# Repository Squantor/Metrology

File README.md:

# General Metrology related projects/tools
This repository contains metrology related hardware/software/mechcanical parts. Stuff like tools, jigs, adapters etc.
## Structure
* [electronics](electronics/README.md) contains all the electronic hardware used in the project.
* [software](software/README.md) contains all the software used in the project. This can be embedded, PC/smartphone or test scripts, anything a computer can execute resides here.
* [mechanical](mechanical/README.md) contains all the CAD drawings, mostly 3d printable objects.
* [documentation](documentation/index.md) contains all project documentation, logs, research, papers, datasheets and more.
## Cloning
This repository makes extensive use of submodules, use ```git clone --recurse-submodules https://github.com/Squantor/Metrology.git``` to clone everything in one go.

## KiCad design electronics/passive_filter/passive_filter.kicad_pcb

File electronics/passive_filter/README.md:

# Passive filter and pad
Small filter and pad PCB
## TODO's
Still some things need to be done:
* schematic entry 
* PCB layout
* Review with one night in between
* Produce at [OSHPARK](https://oshpark.com/)
* Assemble
* Test & characterise
* update Readme.md with pictures and BOM

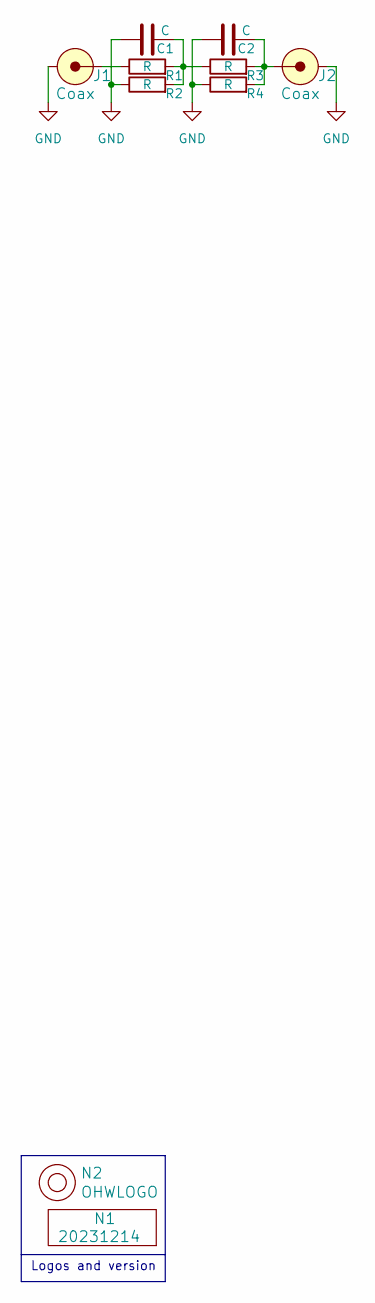
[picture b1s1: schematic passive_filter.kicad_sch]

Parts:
C1, C2: C; C_0402+0603+0805+TH
J1, J2: Coax; coax_edge_1.5_center_5_side
N1: 20231214; Label_Generic
N2: OHWLOGO; OSHW-Symbol_6.7x6mm_SilkScreen
R1, R2, R3, R4: R; R_0805+0603

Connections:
GND: C1.1, C2.1, J1.2, J2.2, R2.1, R4.1
unnamed: C1.2, R1.2, R2.2, R3.1
unnamed: C2.2, J2.1, R3.2, R4.2
unnamed: J1.1, R1.1

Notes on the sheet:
Logos and version

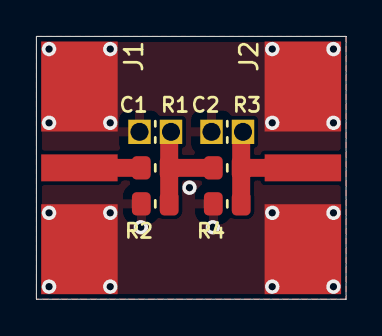
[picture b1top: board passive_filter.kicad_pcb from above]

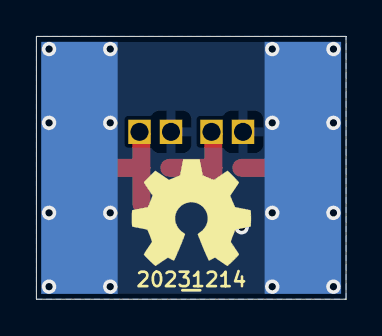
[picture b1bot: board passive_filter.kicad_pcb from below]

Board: 2 copper layers, 17.2 x 14.6 mm, 10 parts (2 on the bottom side), 4 nets.

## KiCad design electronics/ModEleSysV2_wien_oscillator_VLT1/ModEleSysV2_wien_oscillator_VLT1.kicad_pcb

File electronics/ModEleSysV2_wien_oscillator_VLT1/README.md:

# Wien bridge oscillator
Wien bridge oscillator based on the linear technology application note 43 figure 47.

## TODO's
Still some things need to be done:
* Fill in this project description
* schematic entry 
* PCB layout
* Review with one night in between
* Produce at [OSHPARK](https://oshpark.com/)
* Assemble
* Test & characterise
* update Readme.md with pictures and BOM

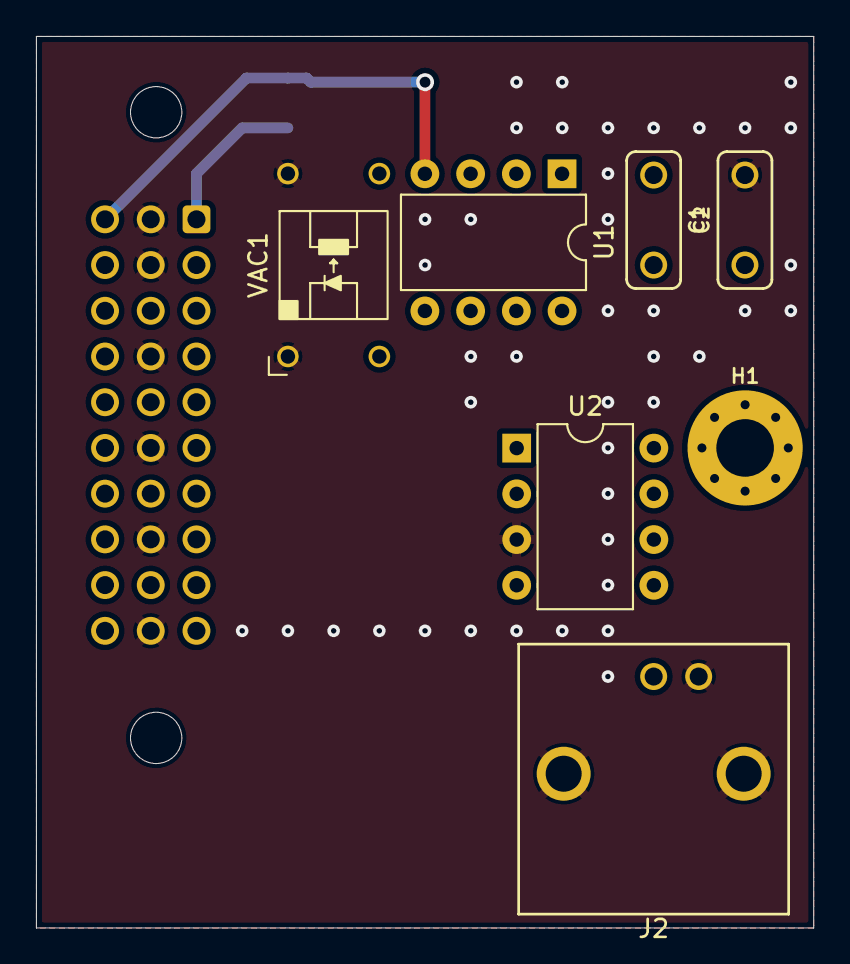
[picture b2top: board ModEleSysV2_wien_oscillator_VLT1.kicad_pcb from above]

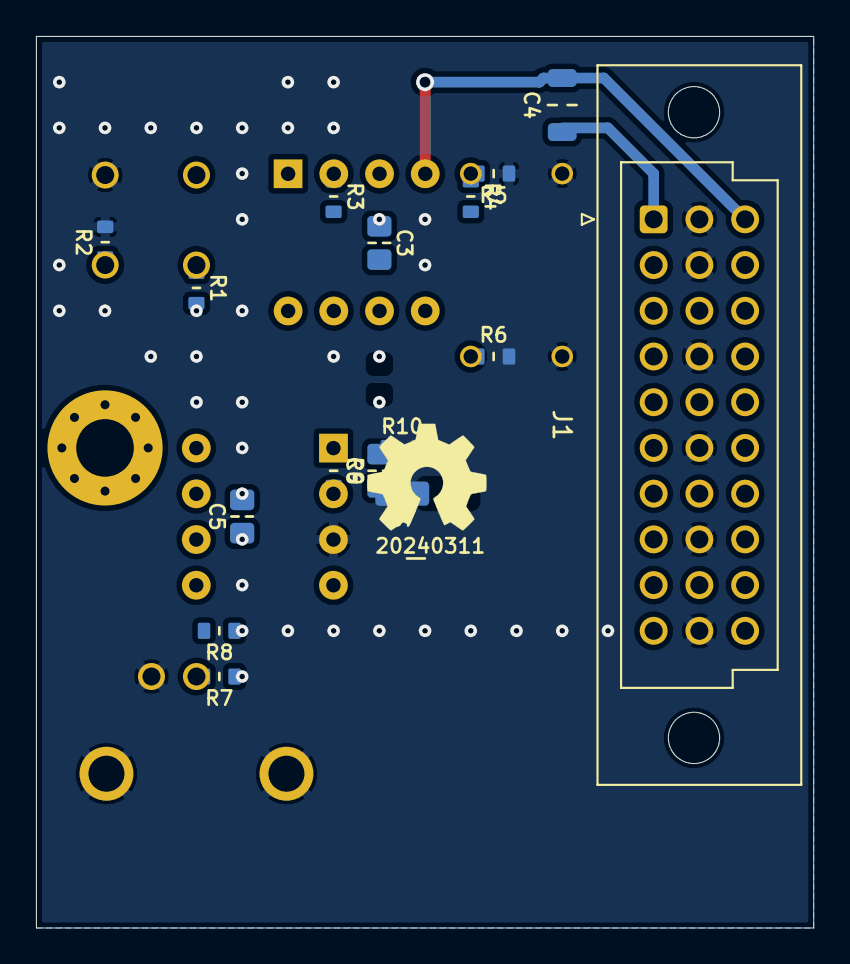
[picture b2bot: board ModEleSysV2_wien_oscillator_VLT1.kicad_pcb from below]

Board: 2 copper layers, 43.2 x 49.5 mm, 25 parts (18 on the bottom side), 13 nets.

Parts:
C1, C2: 47n; C-050-030X100-film
C3, C5, C6: 1uF; C_0805+0603
C4: 10uF; C_1206
C7: 10uF; C_0805+0603
H1: MountingHole; MountingHole_3.2mm_M3_Pad_Via
J1: DIN41612_R3_3x10_Male_Vertical_THT
J2: Coax_shielded; Conn_BNC_RightAngle_TH
N1: 20240311; Label_Generic
N2: OHWLOGO; OSHW-Symbol_6.7x6mm_SilkScreen
R1, R2: 3K; R_0603_hand
R3: 6K8; R_0603_hand
R4: 3K3; R_0603_hand
R5: 220; R_0603_hand
R6: 100; R_0603_hand
R7, R8: 1K2; R_0603_hand
R9: 120K; R_0603_hand
R10: 1K; R_0603_hand
U1: TL081; DIP-8_W7.62mm
U2: LM358; DIP-8_W7.62mm
VAC1: Vactrol; NSL32SR3

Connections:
/+aV: C3.2, C4.1, C5.2, J1.A1 (V+), U1.7 (V+), U2.8 (V+)
/-aV: C3.1, C4.2, C5.1, J1.C1 (V-), U1.4 (V-), U2.4 (V-)
/GAIN_SET: C6.2, R6.2, R9.1, R10.1, U2.1 (OUT1)
/OUT: R1.2, R3.2, R7.1, R8.1, U1.6 (OUT), U2.6 (-IN2), U2.7 (OUT2)
GND: C2.2, J1.B1 (GND), J1.B2 (GND), J1.B4 (GND), J1.B6 (GND), J1.B8 (GND), J1.B10 (GND), J2.2, J2.S, R2.2, R5.1, U2.3 (+IN1), VAC1.1 (C), VAC1.4 (R)
unnamed: C1.2, R1.1
unnamed: C7.1, R10.2
unnamed: J2.1, R7.2, R8.2
unnamed: R4.1, R5.2, VAC1.3 (R)
unnamed: C1.1, C2.1, R2.1, U1.3 (+IN)
unnamed: R3.1, R4.2, U1.2 (-IN)
unnamed: C6.1, C7.2, R9.2, U2.2 (-IN1)
unnamed: R6.1, VAC1.2 (A)

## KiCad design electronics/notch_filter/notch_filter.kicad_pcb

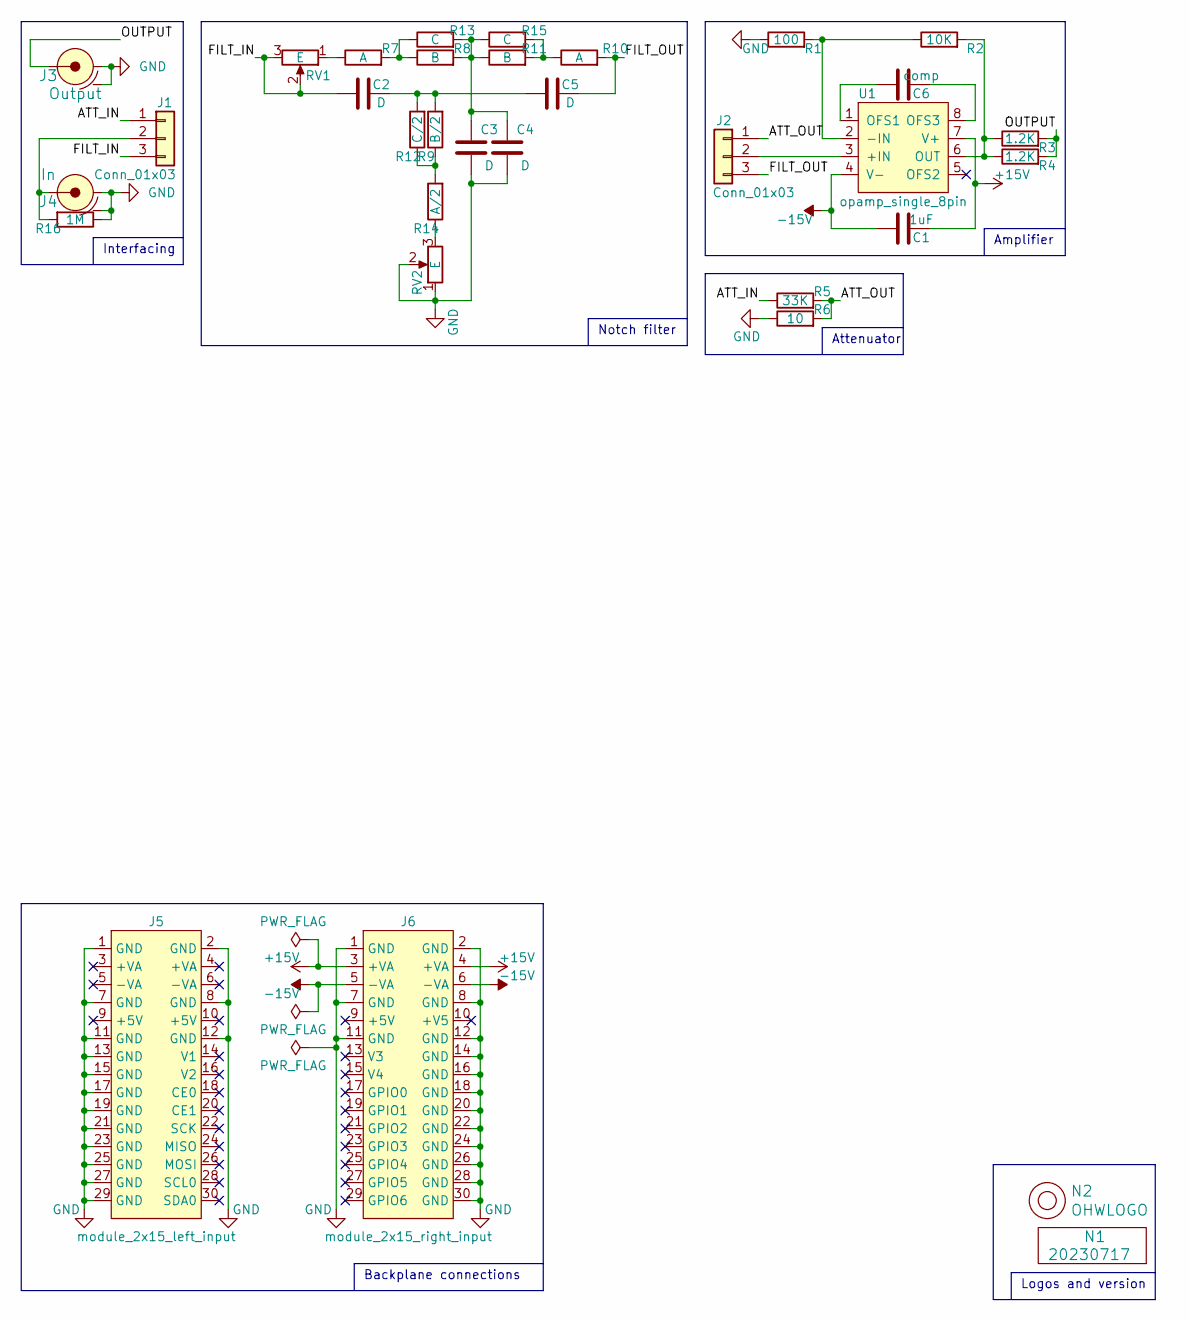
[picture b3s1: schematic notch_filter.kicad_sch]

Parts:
C1: 1uF; C_0805+0603
C2, C3, C4, C5: D; C-050-050X100-0805-3516-film
C6: comp; C_0805+0603
J1, J2: Conn_01x03; JST_PH_B3B-PH-K_1x03_P2.00mm_Vertical
J3: Output; Conn_BNC_RightAngle_TH
J4: In; Conn_BNC_RightAngle_TH
J5: module_2x15_left_input; PinHeader_2x15_P2.54mm_Vertical
J6: module_2x15_right_input; PinHeader_2x15_P2.54mm_Vertical
N1: 20230717; Label_Generic
N2: OHWLOGO; OSHW-Symbol_6.7x6mm_SilkScreen
R1: 100; R_0805+0603
R2: 10K; R_0805+0603
R3, R4: 1.2K; R_0805+0603
R5: 33K; R_0805+0603
R6: 10; R_0805+0603
R7, R10: A; R_0805+0603
R8, R11: B; R_0805+0603
R9: B/2; R_0805+0603
R12: C/2; R_0805+0603
R13, R15: C; R_0805+0603
R14: A/2; R_0805+0603
R16: 1M; R_0805+0603
RV1, RV2: E; Potentiometer_Bourns_3296W_Vertical
U1: opamp_single_8pin; DIP-8_W7.62mm_Socket

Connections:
+15V: C1.2, J6.3 (+VA), J6.4 (+VA), U1.7 (V+)
-15V: C1.1, J6.5 (-VA), J6.6 (-VA), U1.4 (V-)
/ATT_IN: J1.1, R5.1
/ATT_OUT: J2.1, R5.2, R6.2
/FILT_IN: C2.1, J1.3, RV1.2, RV1.3
/FILT_OUT: C5.2, J2.3, R10.2
/OUTPUT: J3.1, R3.2, R4.2
GND: C3.1, C4.1, J3.2, J3.S, J4.2, J4.S, J5.1 (GND), J5.2 (GND), J5.7 (GND), J5.8 (GND), J5.11 (GND), J5.12 (GND), J5.13 (GND), J5.15 (GND), J5.17 (GND), J5.19 (GND), J5.21 (GND), J5.23 (GND), J5.25 (GND), J5.27 (GND), J5.29 (GND), J6.1 (GND), J6.2 (GND), J6.7 (GND), J6.8 (GND), J6.11 (GND), J6.12 (GND), J6.14 (GND), J6.16 (GND), J6.18 (GND), J6.20 (GND), J6.22 (GND), J6.24 (GND), J6.26 (GND), J6.28 (GND), J6.30 (GND), R1.1, R6.1, R16.1, RV2.1, RV2.2
unnamed: C2.2, C5.1, R9.2, R12.2
unnamed: C3.2, C4.2, R8.2, R11.1, R13.2, R15.1
unnamed: J1.2, J4.1, R16.2
unnamed: J2.2, U1.3 (+IN)
unnamed: R7.1, RV1.1
unnamed: R10.1, R11.2, R15.2
unnamed: R9.1, R12.1, R14.2
unnamed: R7.2, R8.1, R13.1
unnamed: R14.1, RV2.3
unnamed: R1.2, R2.1, U1.2 (-IN)
unnamed: C6.1, U1.1 (OFS1)
unnamed: C6.2, U1.8 (OFS3)
unnamed: R2.2, R3.1, R4.1, U1.6 (OUT)

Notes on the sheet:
Logos and version
Amplifier
Backplane connections
Attenuator
Interfacing
Notch filter

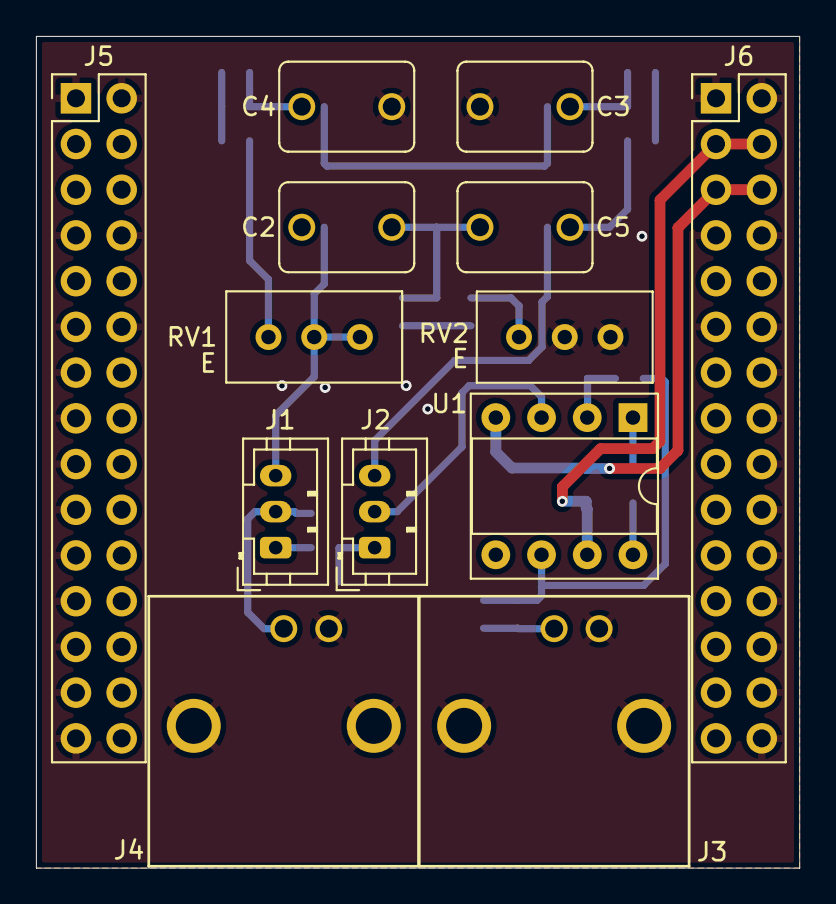
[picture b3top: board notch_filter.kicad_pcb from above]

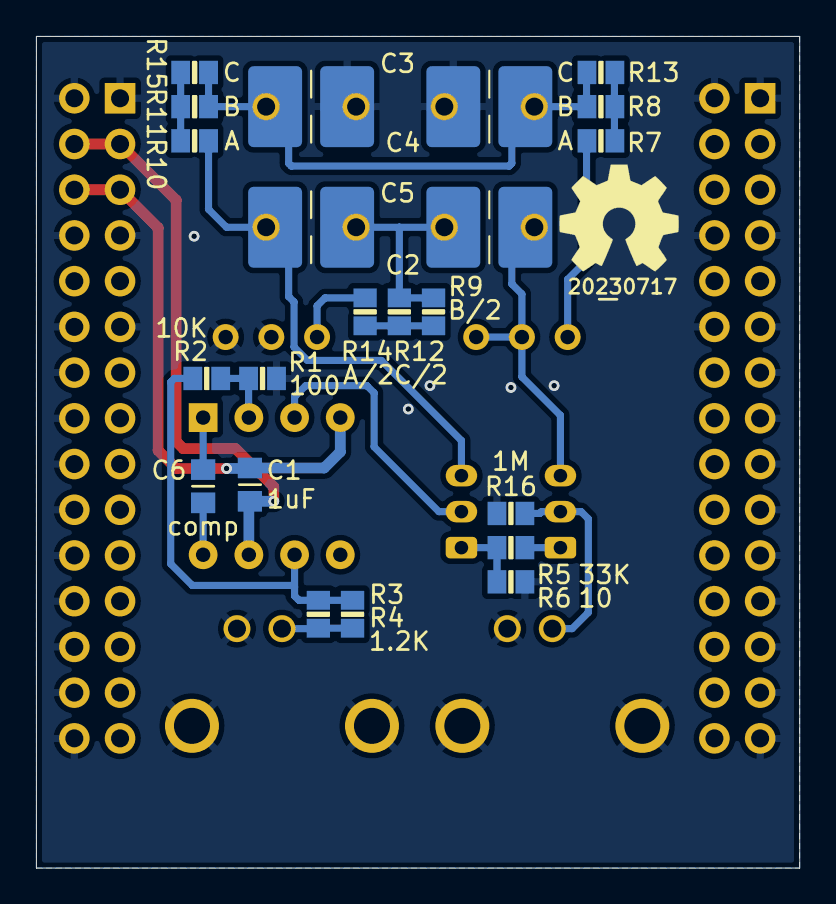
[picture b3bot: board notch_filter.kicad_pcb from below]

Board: 2 copper layers, 42.4 x 46.2 mm, 33 parts (20 on the bottom side), 21 nets.

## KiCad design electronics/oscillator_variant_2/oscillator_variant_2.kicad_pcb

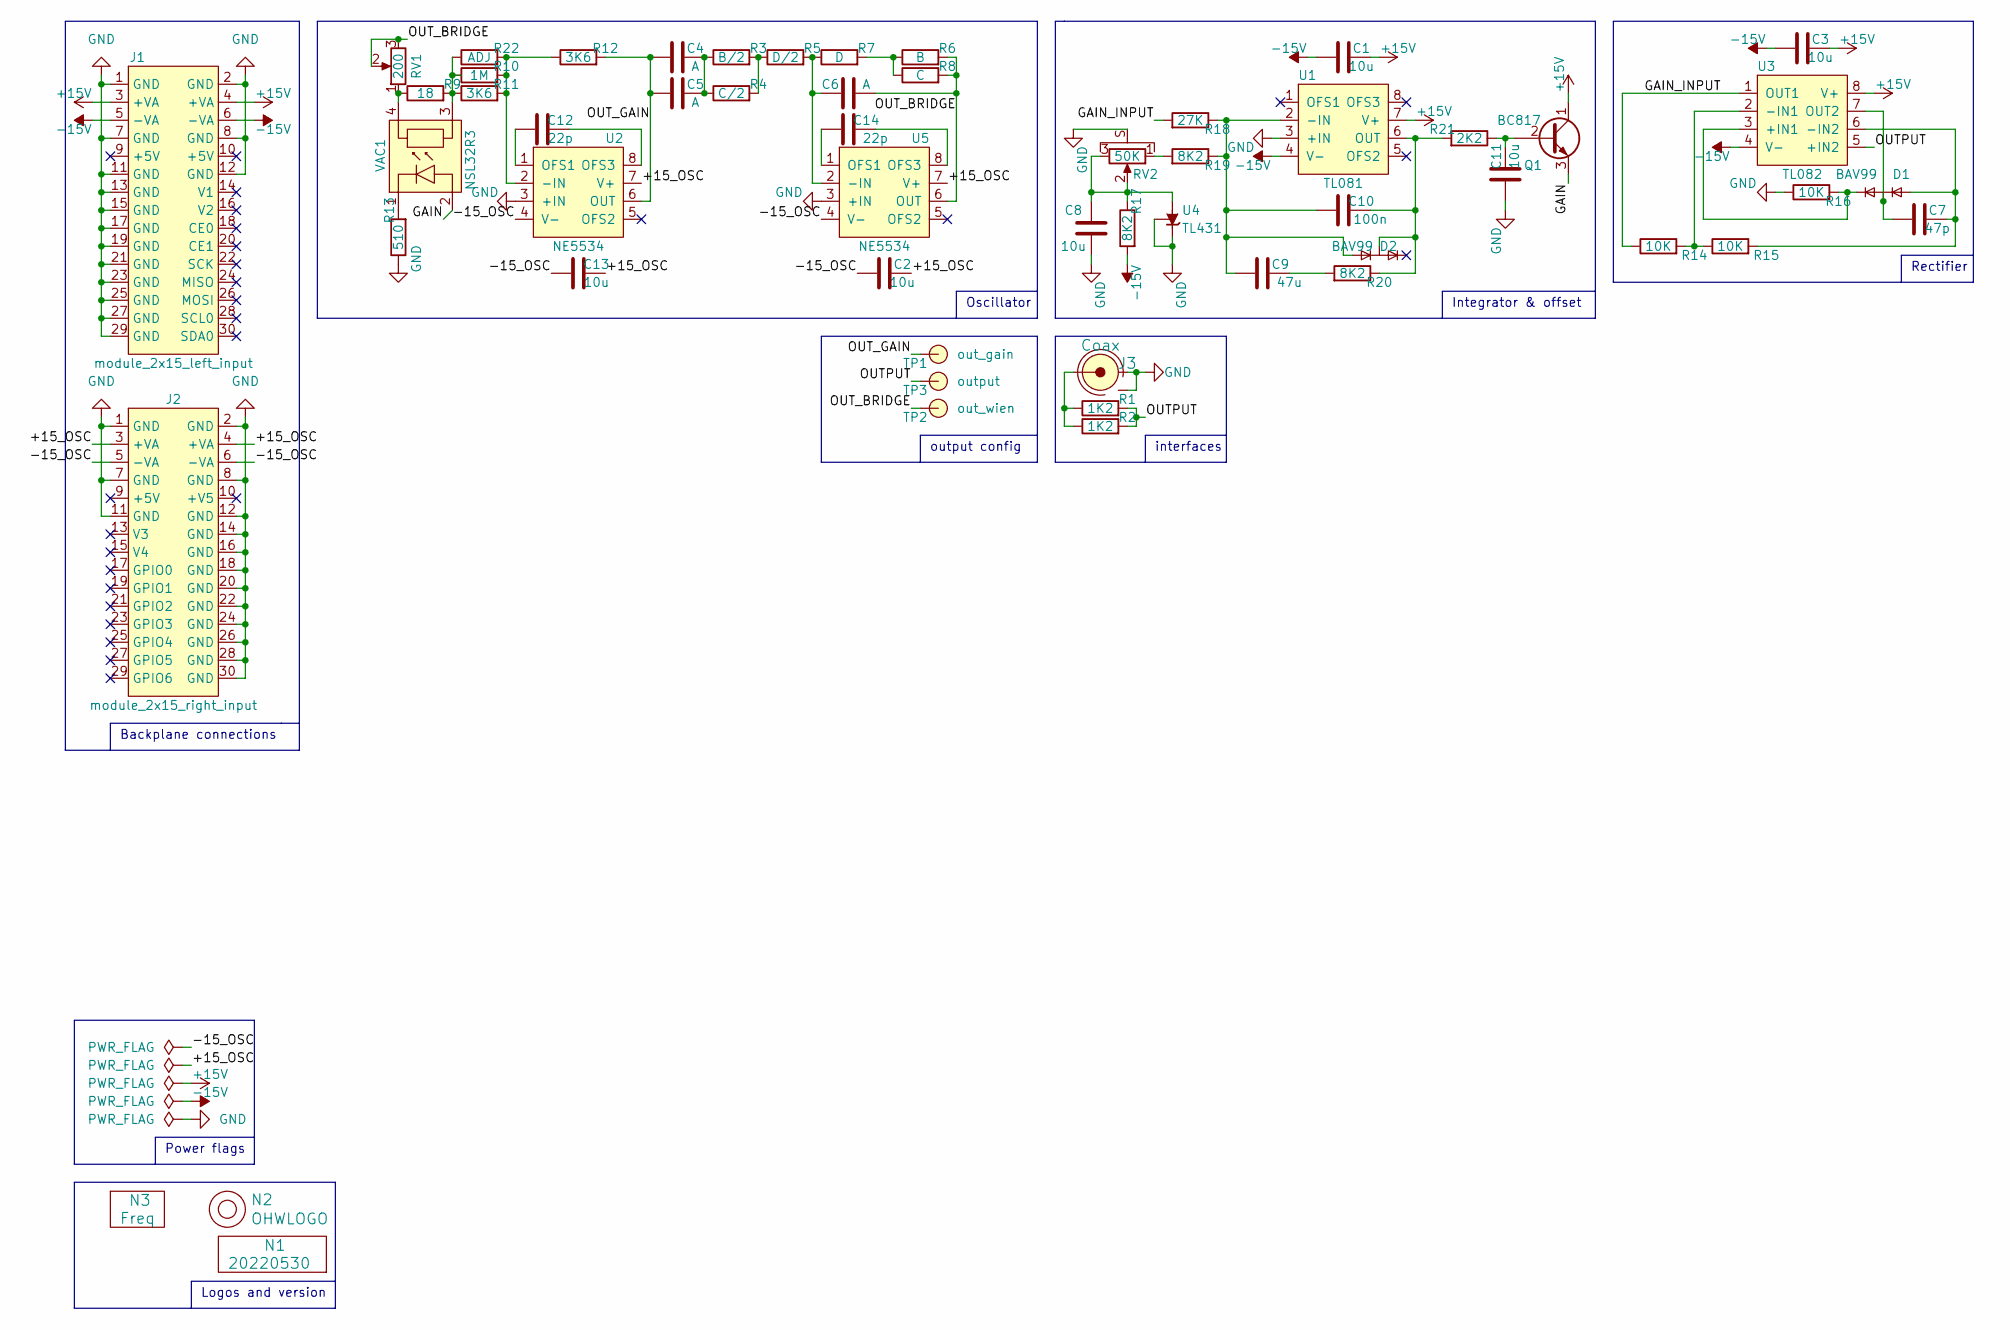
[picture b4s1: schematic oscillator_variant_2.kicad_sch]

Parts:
C1, C2, C3, C8, C11, C13: 10u; C_0805+0603
C4, C5, C6: A; C-050-050X100-0805-3516-film
C7: 47p; C_0805+0603
C9: 47u; C-050-030X100-film
C10: 100n; C-050-030X100-film
C12, C14: 22p; C_0805+0603
D1, D2: BAV99; SOT23-3
J1: module_2x15_left_input; module_2x15_left
J2: module_2x15_right_input; module_2x15_right
J3: Coax; Conn_BNC_RightAngle_TH
N1: 20220530; Label_Generic
N2: OHWLOGO; OSHW-Symbol_6.7x6mm_SilkScreen
N3: Freq; Label_Note_medium
Q1: BC817; SOT23-3
R1, R2: 1K2; R_0603_hand
R3: B/2; R_0805+0603
R4: C/2; R_0805+0603
R5: D/2; R_0805+0603
R6: B; R_0805+0603
R7: D; R_0805+0603
R8: C; R_0805+0603
R9: 18; R_0805+0603
R10: 1M; R_0805+0603
R11, R12: 3K6; R_0805+0603
R13: 510; R_0603_hand
R14, R15, R16: 10K; R_0603_hand
R17, R19, R20: 8K2; R_0603_hand
R18: 27K; R_0603_hand
R21: 2K2; R_0603_hand
R22: ADJ; R_0805+0603
RV1: 200; Potentiometer_Bourns_3296W_Vertical
RV2: 50K; POT_ALPS_RK09K111
TP1: out_gain; TestPoint_hole_H04R07
TP2: out_wien; TestPoint_hole_H04R07
TP3: output; TestPoint_hole_H04R07
U1: TL081; DIP-8_W7.62mm_Socket
U2, U5: NE5534; DIP-8_W7.62mm_Socket
U3: TL082; DIP-8_W7.62mm_Socket
U4: TL431; SOT23-3
VAC1: NSL32R3; NSL32SR3

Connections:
+15V: C1.2, C3.2, J1.3 (+VA), J1.4 (+VA), Q1.1 (C), U1.7 (V+), U3.8 (V+)
-15V: C1.1, C3.1, J1.5 (-VA), J1.6 (-VA), R17.2, U1.4 (V-), U3.4 (V-)
/+15_OSC: C2.2, C13.2, J2.3 (+VA), J2.4 (+VA), U2.7 (V+), U5.7 (V+)
/-15_OSC: C2.1, C13.1, J2.5 (-VA), J2.6 (-VA), U2.4 (V-), U5.4 (V-)
/GAIN: Q1.3 (E), VAC1.2 (A)
/GAIN_INPUT: R14.1, R18.2, U3.1 (OUT1)
/OUTPUT: R1.2, R2.2, TP3.1, U3.5 (+IN2)
/OUT_BRIDGE: C6.2, R6.2, R8.2, RV1.2, RV1.3, TP2.1, U5.6 (OUT)
/OUT_GAIN: C4.1, C5.1, R12.2, TP1.1, U2.6 (OUT)
GND: C8.1, C11.1, J1.1 (GND), J1.2 (GND), J1.7 (GND), J1.8 (GND), J1.11 (GND), J1.12 (GND), J1.13 (GND), J1.15 (GND), J1.17 (GND), J1.19 (GND), J1.21 (GND), J1.23 (GND), J1.25 (GND), J1.27 (GND), J1.29 (GND), J2.1 (GND), J2.2 (GND), J2.7 (GND), J2.8 (GND), J2.11 (GND), J2.12 (GND), J2.14 (GND), J2.16 (GND), J2.18 (GND), J2.20 (GND), J2.22 (GND), J2.24 (GND), J2.26 (GND), J2.28 (GND), J2.30 (GND), J3.2, J3.S, R13.1, R16.1, RV2.S (shield), U1.3 (+IN), U2.3 (+IN), U4.1 (REF), U4.3 (K), U5.3 (+IN)
unnamed: C4.2, C5.2, R3.1, R4.1
unnamed: C6.1, R5.2, R7.1, U5.2 (-IN)
unnamed: C7.1, D1.3 (K1A2), U3.7 (OUT2)
unnamed: C7.2, D1.1 (A1), R15.2, U3.6 (-IN2)
unnamed: C8.2, R17.1, RV2.2, RV2.3, U4.2 (A)
unnamed: C9.2, R20.2
unnamed: C9.1, C10.1, D2.1 (A1), R18.1, R19.1, U1.2 (-IN)
unnamed: C10.2, D2.3 (K1A2), R20.1, R21.2, U1.6 (OUT)
unnamed: C11.2, Q1.2 (B), R21.1
unnamed: C12.1, U2.1 (OFS1)
unnamed: C12.2, U2.8 (OFS3)
unnamed: C14.1, U5.1 (OFS1)
unnamed: C14.2, U5.8 (OFS3)
unnamed: D1.2 (K2), R16.2, U3.3 (+IN1)
unnamed: J3.1, R1.1, R2.1
unnamed: R3.2, R4.2, R5.1
unnamed: R6.1, R7.2, R8.1
unnamed: R9.1, RV1.1, VAC1.4 (R)
unnamed: R9.2, R10.1, R11.1, R22.1, VAC1.3 (R)
unnamed: R10.2, R11.2, R12.1, R22.2, U2.2 (-IN)
unnamed: R13.2, VAC1.1 (C)
unnamed: R14.2, R15.1, U3.2 (-IN1)
unnamed: R19.2, RV2.1

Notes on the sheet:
Backplane connections
Oscillator
Logos and version
interfaces
output config
Power flags
Integrator & offset
Rectifier

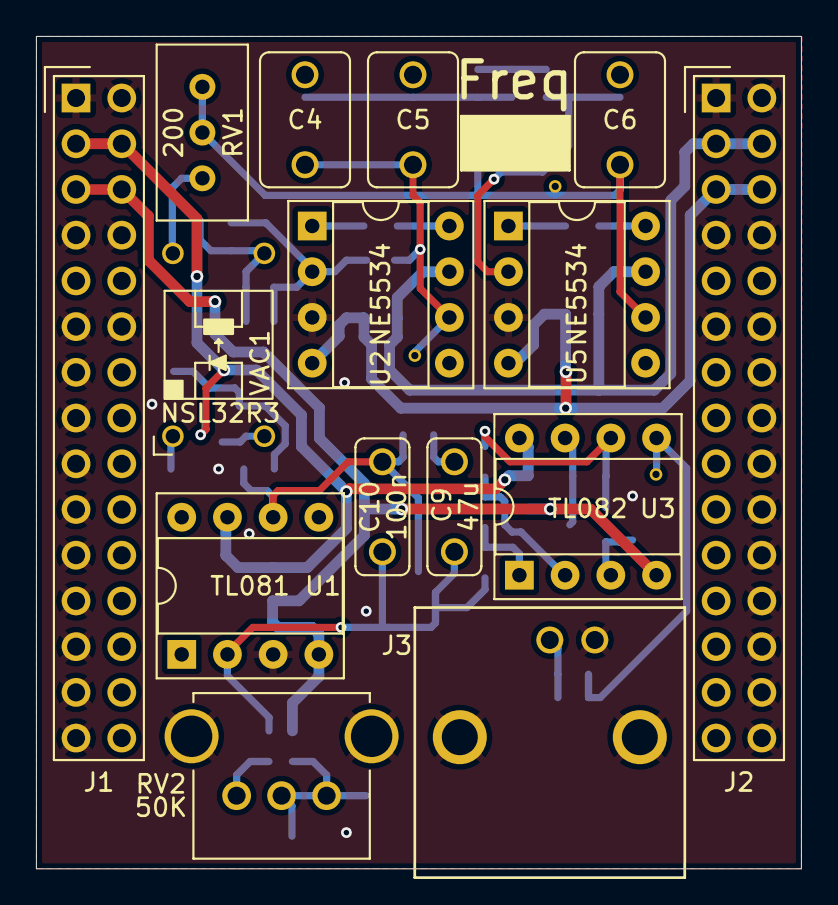
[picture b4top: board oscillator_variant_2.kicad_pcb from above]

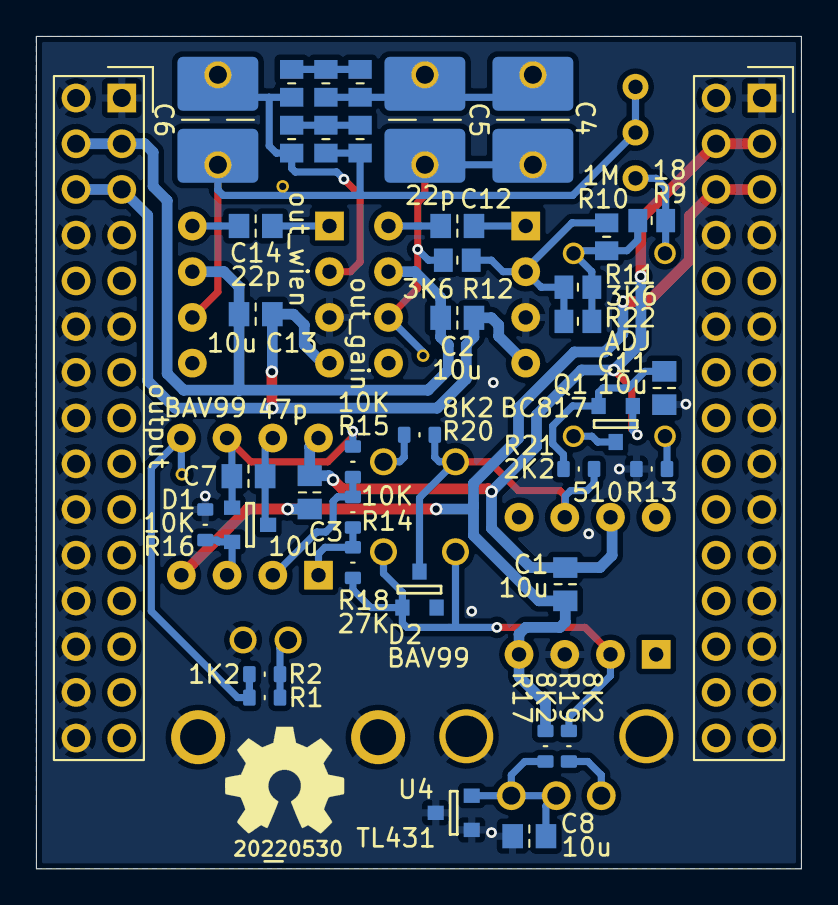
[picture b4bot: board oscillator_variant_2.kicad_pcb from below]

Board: 2 copper layers, 42.5 x 46.2 mm, 56 parts (40 on the bottom side), 33 nets.

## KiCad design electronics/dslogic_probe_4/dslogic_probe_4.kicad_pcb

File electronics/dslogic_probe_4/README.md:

# 4 channel dslogic probe tip
4 channel logic analyser probe tip designed for the DSlogic logic analyzer
## TODO's
Still some things need to be done:
* PCB layout
* Review with one night in between
* Produce at [OSHPARK](https://oshpark.com/)
* Assemble
* Test & characterise
* update Readme.md with pictures and BOM
## BOM
* 4 pin 1.27mm pinheader and 4 pin female 1.27mm pinheader

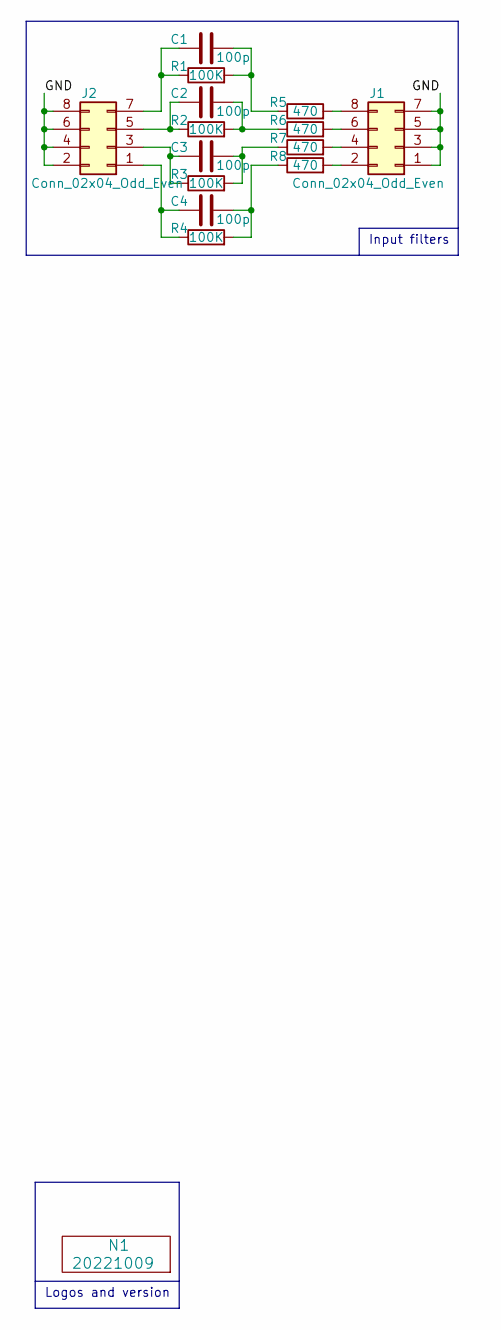
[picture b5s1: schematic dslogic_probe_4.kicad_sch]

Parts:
C1, C2, C3, C4: 100p; C_0402
J1, J2: Conn_02x04_Odd_Even; Header-0127-2X04-EDGE
N1: 20221009; Label_Generic
R1, R2, R3, R4: 100K; R_0402_hand
R5, R6, R7, R8: 470; R_0402_hand

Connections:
/GND: J1.1, J1.3, J1.5, J1.7, J2.2, J2.4, J2.6, J2.8
unnamed: C1.1, J2.7, R1.1
unnamed: C1.2, R1.2, R5.1
unnamed: C2.1, J2.5, R2.1
unnamed: C2.2, R2.2, R6.1
unnamed: C3.1, J2.3, R3.1
unnamed: C3.2, R3.2, R7.1
unnamed: C4.1, J2.1, R4.1
unnamed: C4.2, R4.2, R8.1
unnamed: J1.2, R8.2
unnamed: J1.4, R7.2
unnamed: J1.6, R6.2
unnamed: J1.8, R5.2

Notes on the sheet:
Logos and version
Input filters

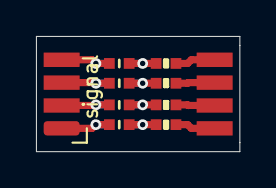
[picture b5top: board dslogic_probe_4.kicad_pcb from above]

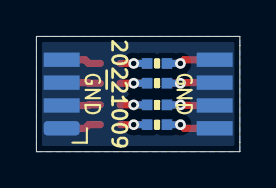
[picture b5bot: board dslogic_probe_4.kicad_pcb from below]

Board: 2 copper layers, 11.3 x 6.4 mm, 15 parts (6 on the bottom side), 13 nets.

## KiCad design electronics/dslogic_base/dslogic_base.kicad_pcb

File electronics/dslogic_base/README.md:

# DSLogic Pro base connection
Breakout board for [DSLogic](https://www.dreamsourcelab.com/product/dslogic-series/) logic analyser. Breaks out the 16 bit port to a flatcable. These flatcables themselves terminate into groups of 4/8 probes.
## TODO's
Still some things need to be done:
* Review with one night in between
* Produce at [OSHPARK](https://oshpark.com/)
* Assemble
* Test & characterise
* update Readme.md with pictures and BOM
## BOM
* Angled 1.27mm header

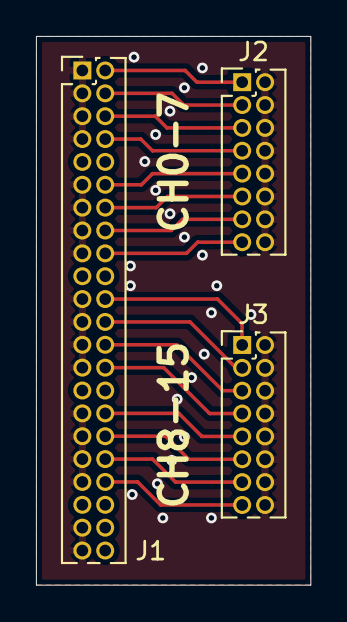
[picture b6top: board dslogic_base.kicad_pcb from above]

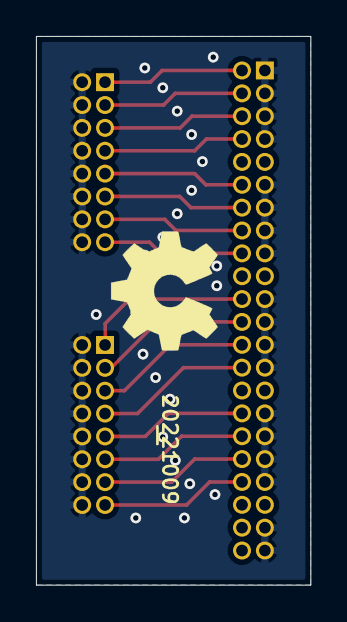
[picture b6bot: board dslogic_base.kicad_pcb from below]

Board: 2 copper layers, 15.2 x 30.5 mm, 5 parts (2 on the bottom side), 17 nets.

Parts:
J1: Conn_02x23_Odd_Even; PinHeader_2x22_P1.27mm_Vertical
J2, J3: Conn_02x08_Odd_Even; PinHeader_2x08_P1.27mm_Vertical
N1: 20221009; Label_Generic
N2: OHWLOGO; OSHW-Symbol_6.7x6mm_SilkScreen

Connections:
/CH00: J1.2, J2.1
/CH01: J1.4, J2.3
/CH02: J1.6, J2.5
/CH03: J1.8, J2.7
/CH04: J1.12, J2.9
/CH05: J1.14, J2.11
/CH06: J1.16, J2.13
/CH07: J1.18, J2.15
/CH08: J1.22, J3.1
/CH09: J1.24, J3.3
/CH10: J1.26, J3.5
/CH11: J1.28, J3.7
/CH12: J1.32, J3.9
/CH13: J1.34, J3.11
/CH14: J1.36, J3.13
/CH15: J1.38, J3.15
GND: J1.1, J1.3, J1.5, J1.7, J1.11, J1.13, J1.15, J1.17, J1.21, J1.23, J1.25, J1.27, J1.31, J1.33, J1.35, J1.37, J1.41, J1.43, J2.2, J2.4, J2.6, J2.8, J2.10, J2.12, J2.14, J2.16, J3.2, J3.4, J3.6, J3.8, J3.10, J3.12, J3.14, J3.16

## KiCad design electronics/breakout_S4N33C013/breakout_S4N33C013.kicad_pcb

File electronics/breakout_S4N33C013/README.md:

# S4N33C013 breakout board
Breakout board for the [S4N33C013](https://www.broadcom.com/products/optical-sensors/silicon-photomultiplier-sipm/afbr-s4n33c013) Silicon Photomultiplier (SiPM)
## TODO's
Still some things need to be done:
* schematic entry 
* PCB layout
* Review with one night in between
* Produce at [OSHPARK](https://oshpark.com/)
* Assemble
* Test & characterise
* update Readme.md with pictures and BOM
## BOM
* [S4N33C013](https://nl.farnell.com/3518030) SiPM
* PCB edge SMA connector
* SMT 2 pin JST connector

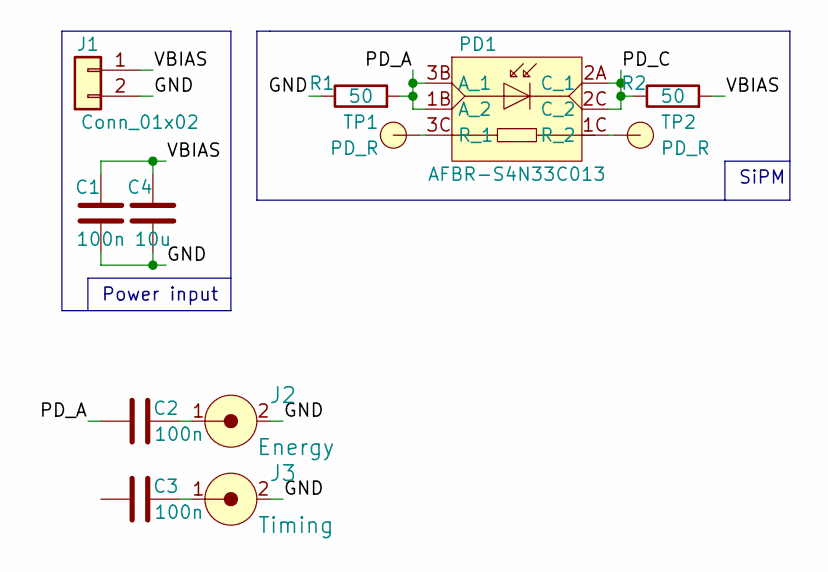
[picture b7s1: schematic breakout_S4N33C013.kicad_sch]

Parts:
C1, C2, C3: 100n; C_0402
C4: 10u; C_1206
J1: Conn_01x02; JST_PH_B2B-PH-SM4-TB_1x02-1MP_P2.00mm_Vertical
J2: Energy; SMA_edge_6mm2
J3: Timing; SMA_edge_6mm2
PD1: AFBR-S4N33C013
R1, R2: 50; R_0603
TP1, TP2: PD_R; TestPoint_pad_circle_D05

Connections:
/GND: C1.1, C4.1, J1.2, J2.2, J3.2, R1.1
/PD_A: C2.2, PD1.1B (A_2), PD1.3B (A_1), R1.2
/PD_C: PD1.2A (C_1), PD1.2C (C_2), R2.1
/VBIAS: C1.2, C4.2, J1.1, R2.2
unnamed: C2.1, J2.1
unnamed: C3.1, J3.1
unnamed: PD1.1C (R_2), TP2.1
unnamed: PD1.3C (R_1), TP1.1

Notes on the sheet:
Power input
SiPM

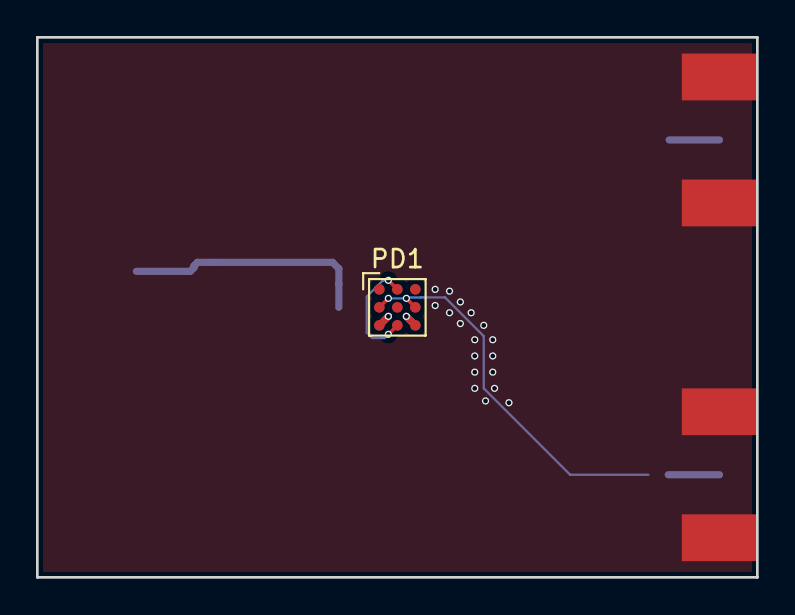
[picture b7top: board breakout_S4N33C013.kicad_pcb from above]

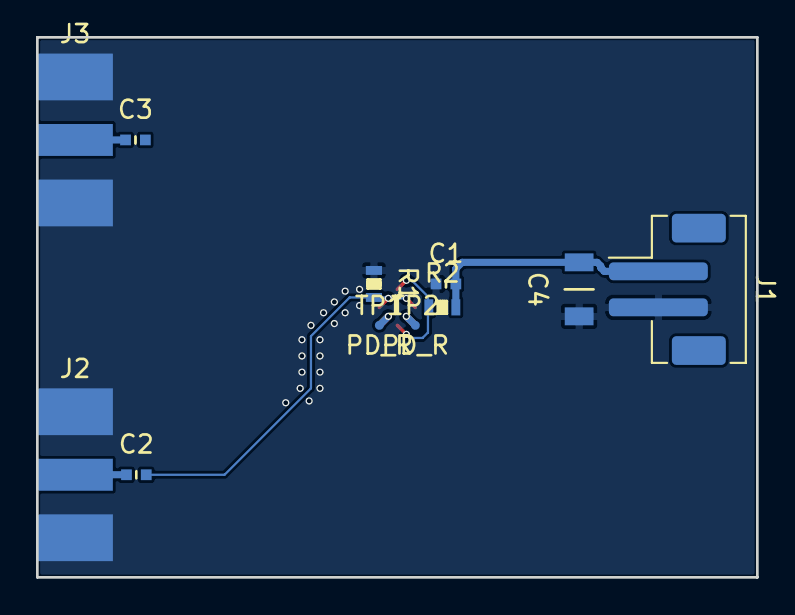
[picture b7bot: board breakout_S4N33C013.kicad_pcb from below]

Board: 4 copper layers, 40.0 x 30.0 mm, 12 parts (11 on the bottom side), 8 nets.
